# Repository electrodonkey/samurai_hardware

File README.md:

# samurai_hardware
Sumo Robot - Main Board

## Description

This repository contains the hardware design files for the main board of the HIRO 2024 sumo robot. The main board is responsible for the following tasks:

- Running the control algorithm
- Optical sensor reading
- Reading IMU data
- Communicating with the motor drivers

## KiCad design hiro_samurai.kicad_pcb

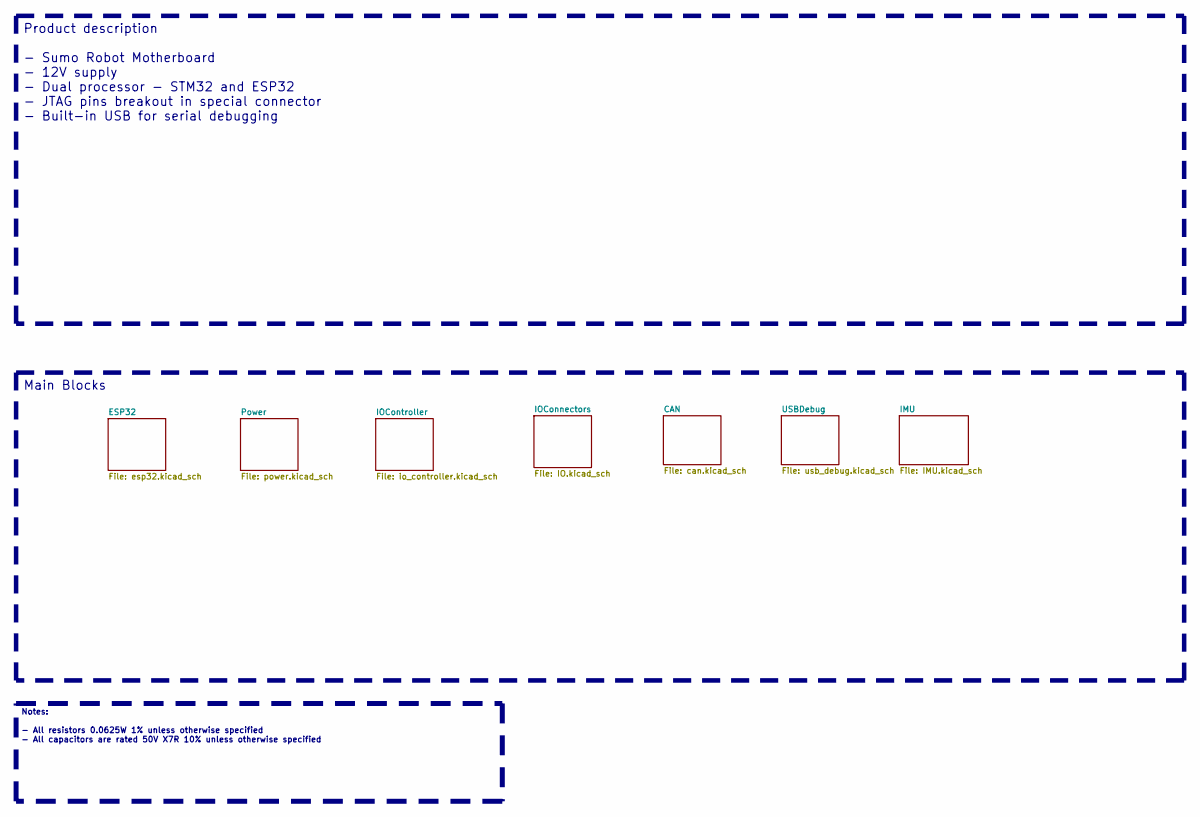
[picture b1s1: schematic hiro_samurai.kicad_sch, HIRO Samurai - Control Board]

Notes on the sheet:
Product description - Sumo Robot Motherboard - 12V supply - Dual processor - STM32 and ESP32 - JTAG pins breakout in special connector - Built-in USB for serial debugging
Notes: - All resistors 0.0625W 1% unless otherwise specified - All capacitors are rated 50V X7R 10% unless otherwise specified
Main Blocks

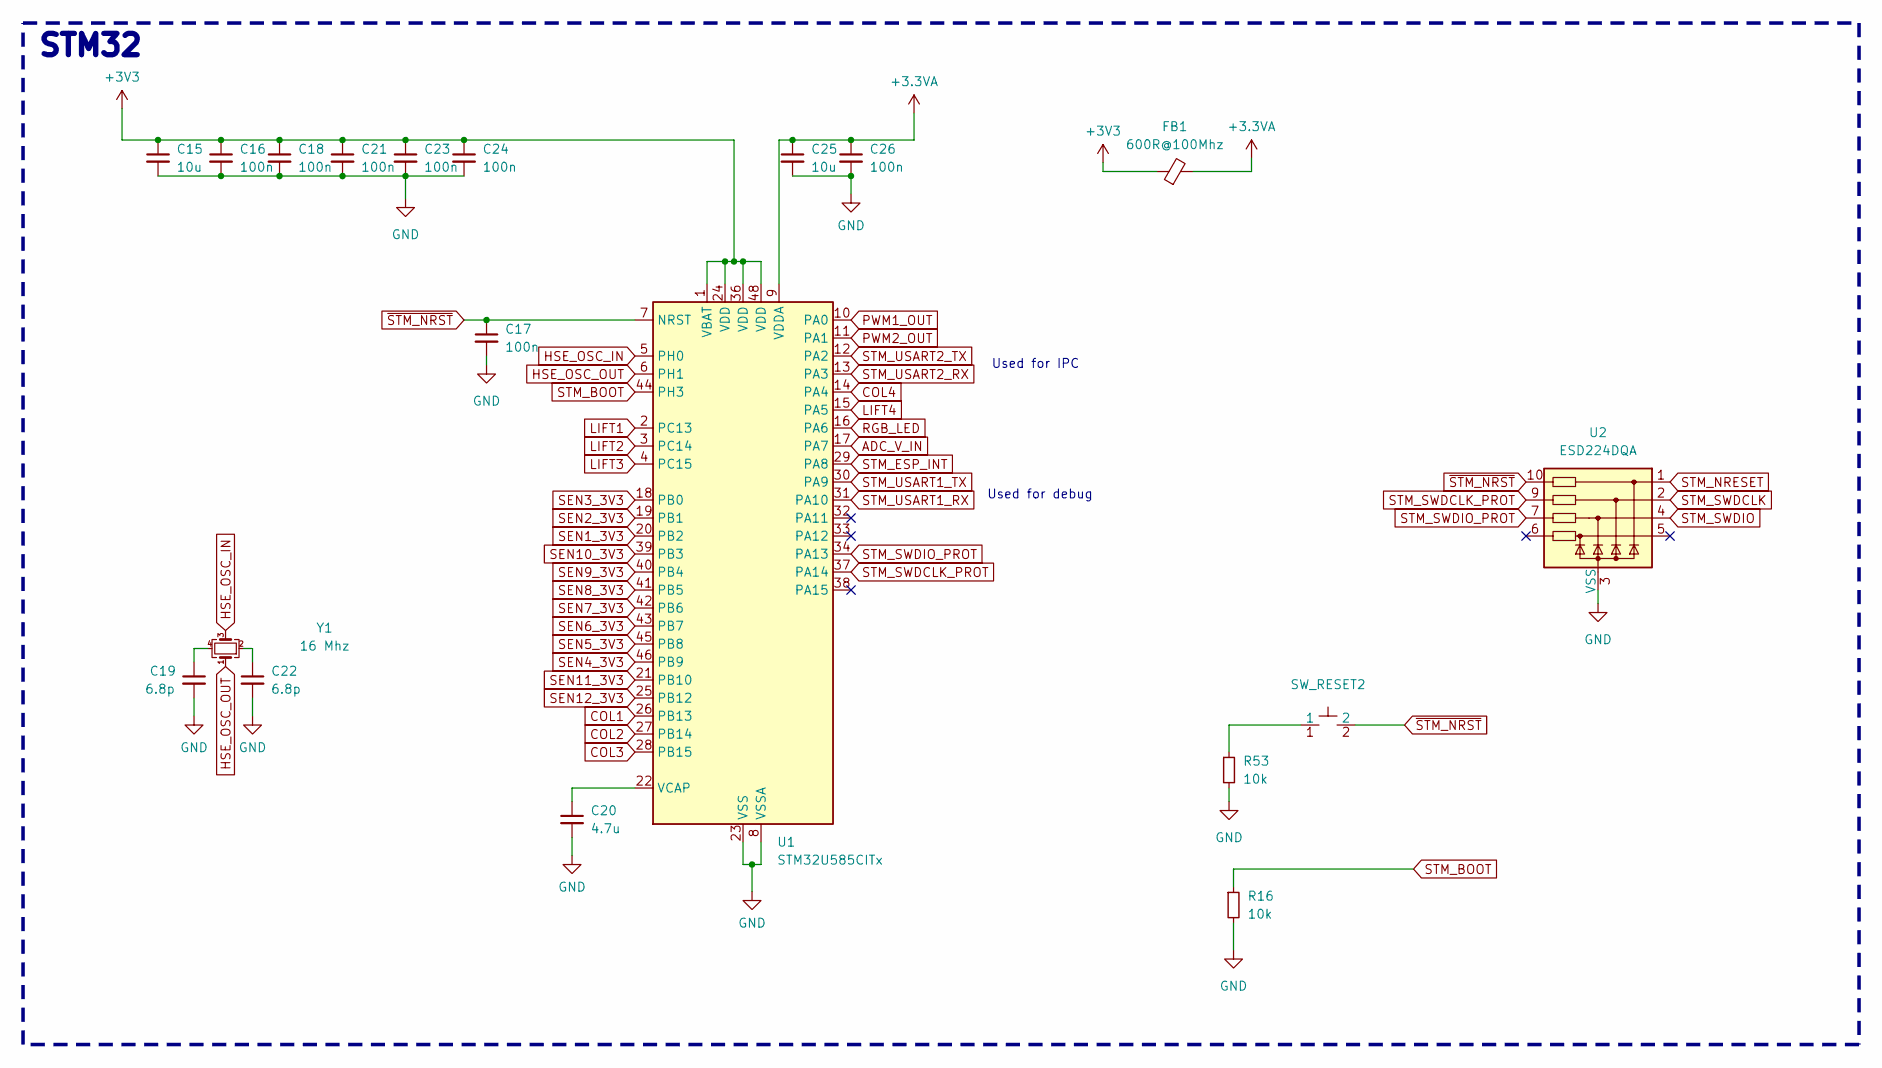
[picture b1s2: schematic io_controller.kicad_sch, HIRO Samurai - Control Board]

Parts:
C15, C25: 10u; C_0603_1608Metric_Pad1.08x0.95mm_HandSolder
C16, C18, C21, C23, C24, C26: 100n; C_0603_1608Metric_Pad1.08x0.95mm_HandSolder
C17: 100n; C_0402_1005Metric_Pad0.74x0.62mm_HandSolder
C19, C22: 6.8p; C_0402_1005Metric_Pad0.74x0.62mm_HandSolder
C20: 4.7u; C_0603_1608Metric_Pad1.08x0.95mm_HandSolder
FB1: 600R@100Mhz; L_0603_1608Metric_Pad1.05x0.95mm_HandSolder
R16, R53: 10k; R_0402_1005Metric_Pad0.72x0.64mm_HandSolder
SW_RESET2: TL1017AABF160QG
U1: STM32U585CITx; LQFP-48_7x7mm_P0.5mm
U2: ESD224DQA; Diodes_UDFN-10_1.0x2.5mm_P0.5mm
Y1: 16 Mhz; Crystal_SMD_2016-4Pin_2.0x1.6mm

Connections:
+3.3VA: C25.1, C26.1, FB1.2, U1.9 (VDDA)
+3V3: C15.1, C16.1, C18.1, C21.1, C23.1, C24.1, FB1.1, U1.1 (VBAT), U1.24 (VDD), U1.36 (VDD), U1.48 (VDD); also elsewhere on the board
ADC_V_IN: U1.17 (PA7); also elsewhere on the board
COL1: U1.26 (PB13); also elsewhere on the board
COL2: U1.27 (PB14); also elsewhere on the board
COL3: U1.28 (PB15); also elsewhere on the board
COL4: U1.14 (PA4); also elsewhere on the board
GND: C15.2, C16.2, C17.2, C18.2, C19.2, C20.2, C21.2, C22.2, C23.2, C24.2, C25.2, C26.2, R16.2, R53.2, U1.8 (VSSA), U1.23 (VSS), U1.35 (VSS), U1.47 (VSS), U2.3 (VSS), U2.8 (VSS); also elsewhere on the board
HSE_OSC_IN: U1.5 (PH0), Y1.3
HSE_OSC_OUT: U1.6 (PH1), Y1.1
LIFT1: U1.2 (PC13); also elsewhere on the board
LIFT2: U1.3 (PC14); also elsewhere on the board
LIFT3: U1.4 (PC15); also elsewhere on the board
LIFT4: U1.15 (PA5); also elsewhere on the board
unnamed: C19.1, Y1.4
unnamed: C22.1, Y1.2
unnamed: R53.1, SW_RESET2.1
unnamed: C20.1, U1.22 (VCAP)
PWM1_OUT: U1.10 (PA0); also elsewhere on the board
PWM2_OUT: U1.11 (PA1); also elsewhere on the board
RGB_LED: U1.16 (PA6); also elsewhere on the board
SEN1_3V3: U1.20 (PB2); also elsewhere on the board
SEN2_3V3: U1.19 (PB1); also elsewhere on the board
SEN3_3V3: U1.18 (PB0); also elsewhere on the board
SEN4_3V3: U1.46 (PB9); also elsewhere on the board
SEN5_3V3: U1.45 (PB8); also elsewhere on the board
SEN6_3V3: U1.43 (PB7); also elsewhere on the board
SEN7_3V3: U1.42 (PB6); also elsewhere on the board
SEN8_3V3: U1.41 (PB5); also elsewhere on the board
SEN9_3V3: U1.40 (PB4); also elsewhere on the board
SEN10_3V3: U1.39 (PB3); also elsewhere on the board
SEN11_3V3: U1.21 (PB10); also elsewhere on the board
SEN12_3V3: U1.25 (PB12); also elsewhere on the board
STM_BOOT: R16.1, U1.44 (PH3)
STM_ESP_INT: U1.29 (PA8); also elsewhere on the board
STM_NRESET: U2.1; also elsewhere on the board
STM_SWDCLK: U2.2; also elsewhere on the board
STM_SWDCLK_PROT: U1.37 (PA14), U2.9
STM_SWDIO: U2.4; also elsewhere on the board
STM_SWDIO_PROT: U1.34 (PA13), U2.7
STM_USART1_RX: U1.31 (PA10); also elsewhere on the board
STM_USART1_TX: U1.30 (PA9); also elsewhere on the board
STM_USART2_RX: U1.13 (PA3); also elsewhere on the board
STM_USART2_TX: U1.12 (PA2); also elsewhere on the board
~STM_NRST: C17.1, SW_RESET2.2, U1.7 (NRST), U2.10

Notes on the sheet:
Used for IPC
Used for debug
STM32

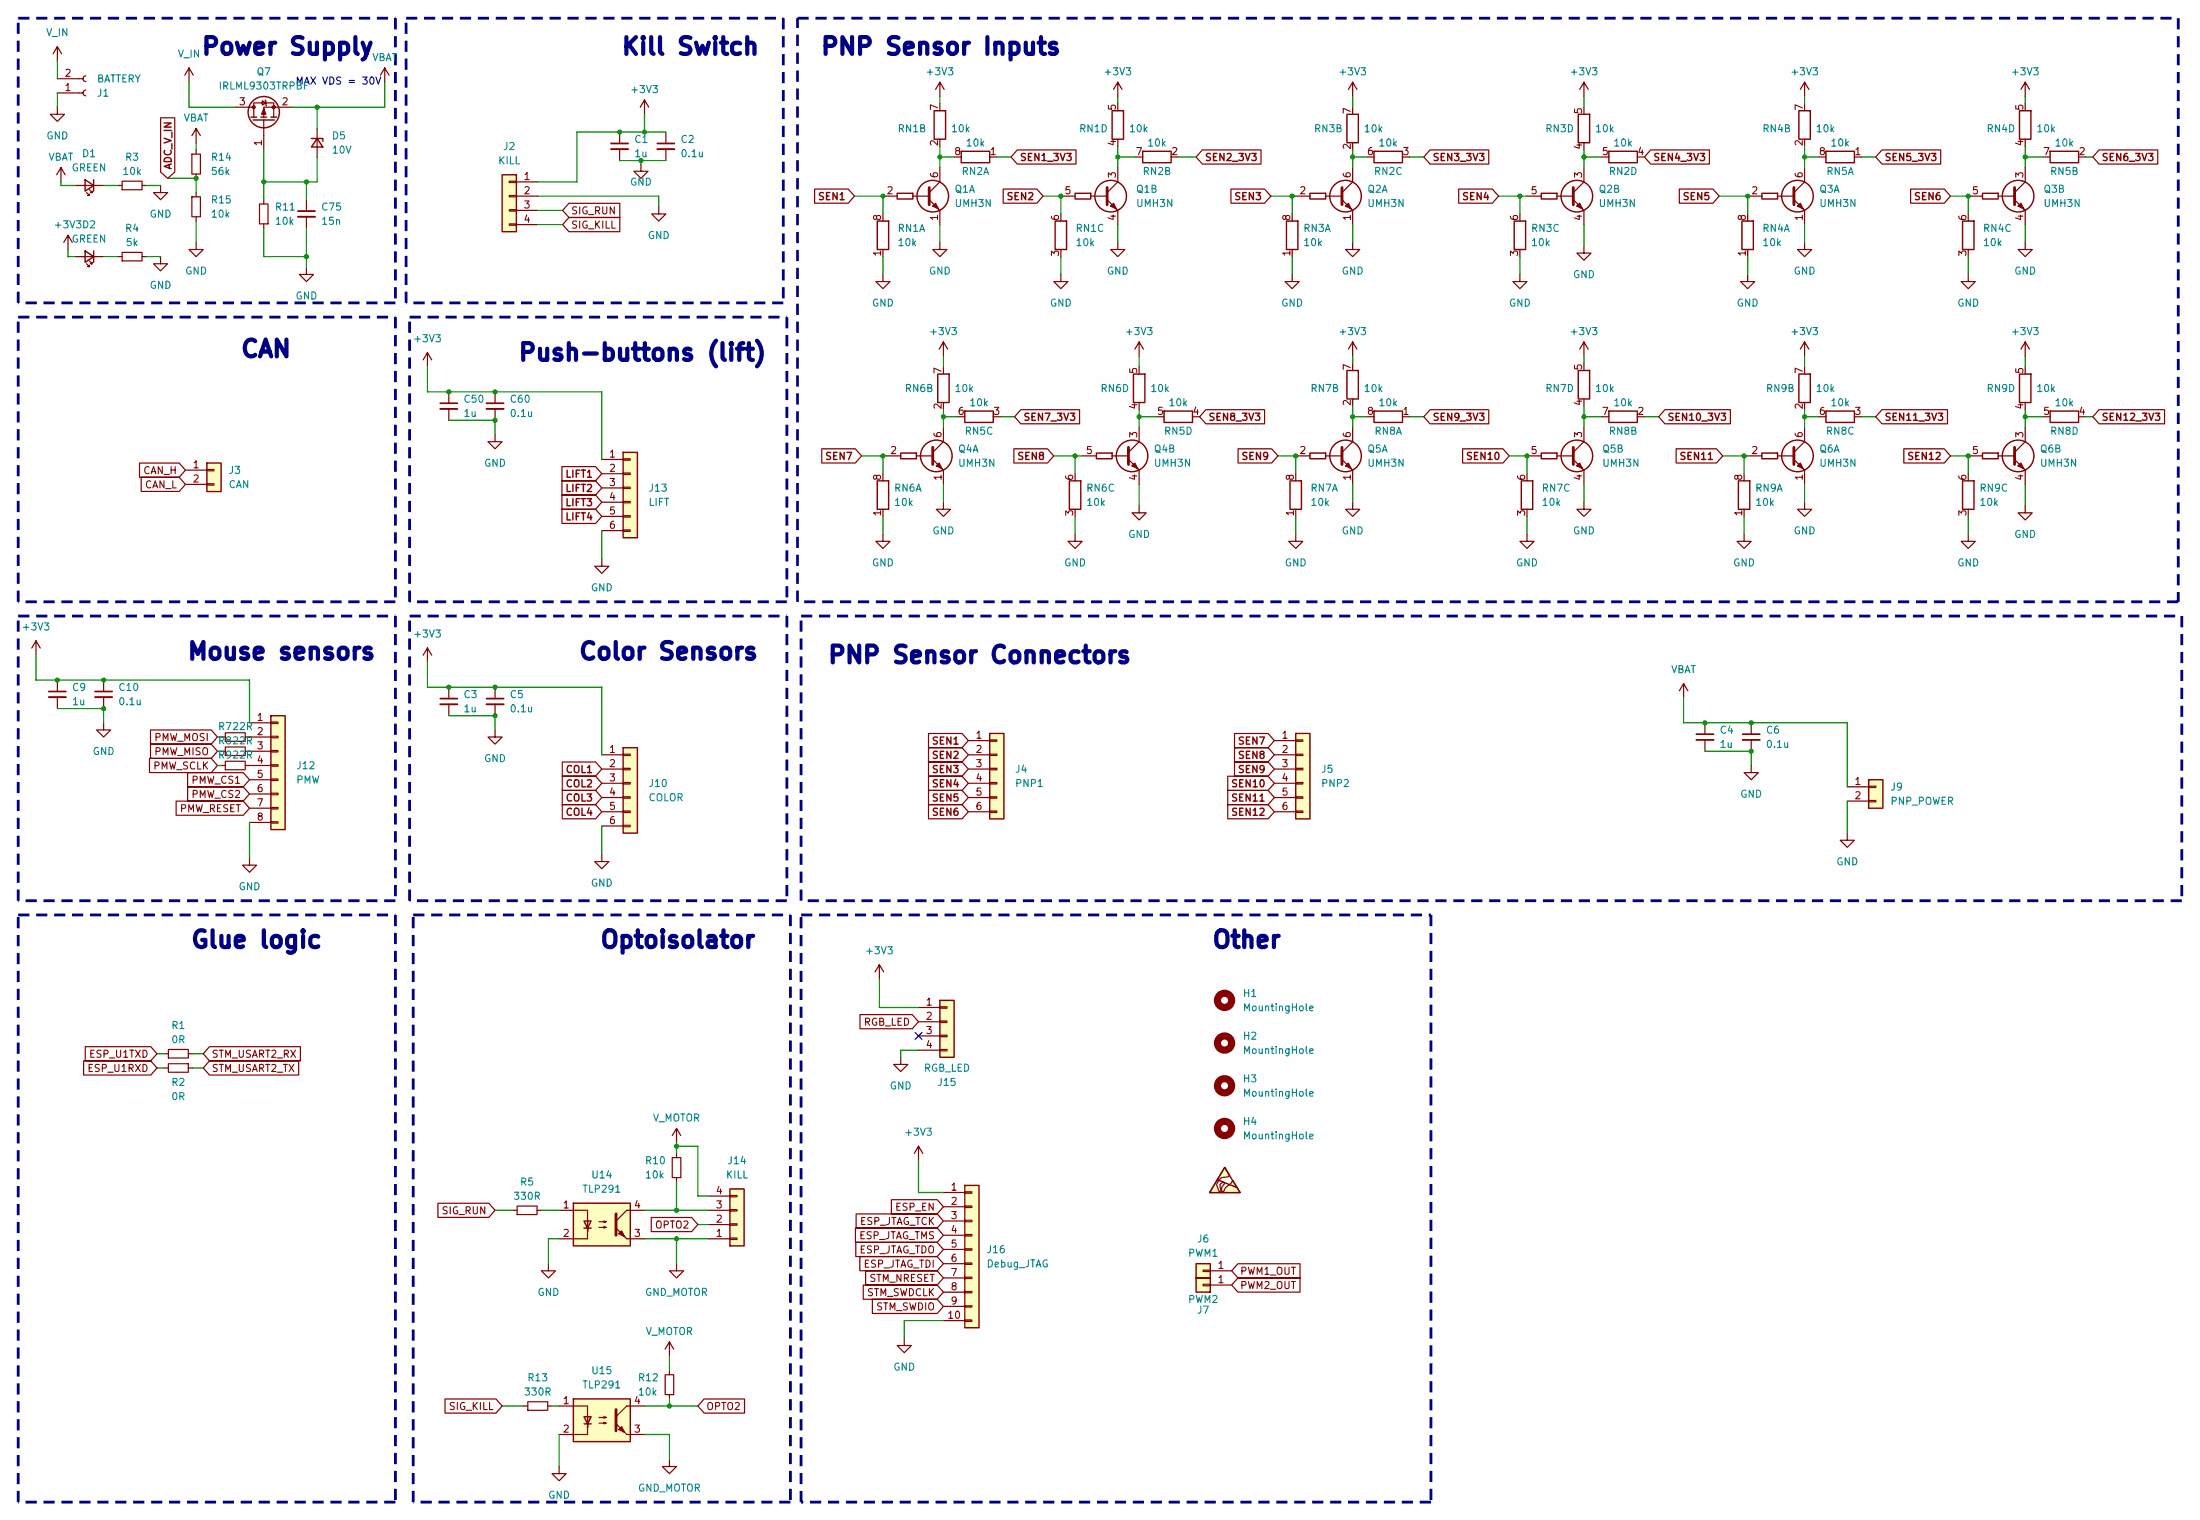
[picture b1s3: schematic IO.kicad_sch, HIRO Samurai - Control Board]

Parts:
C1, C3, C9, C50: 1u; C_0603_1608Metric
C2, C5, C10, C60: 0.1u; C_0603_1608Metric
C4: 1u; C_1210_3225Metric_Pad1.33x2.70mm_HandSolder
C6: 0.1u; C_0805_2012Metric_Pad1.18x1.45mm_HandSolder
C75: 15n; C_0603_1608Metric_Pad1.08x0.95mm_HandSolder
D1, D2: GREEN; LED_0603_1608Metric_Pad1.05x0.95mm_HandSolder
D5: 10V; D_SOD-123
H1, H2, H3, H4: MountingHole; MountingHole_3.2mm_M3
J1: BATTERY; AMASS_XT30U-M_1x02_P5.0mm_Vertical
J2, J14: KILL; Molex_Nano-Fit_105309-xx04_1x04_P2.50mm_Vertical
J3: CAN; Molex_Nano-Fit_105309-xx02_1x02_P2.50mm_Vertical
J4: PNP1; Molex_Nano-Fit_105309-xx06_1x06_P2.50mm_Vertical
J5: PNP2; Molex_Nano-Fit_105309-xx06_1x06_P2.50mm_Vertical
J6: PWM1; SolderWirePad_1x01_SMD_1x2mm
J7: PWM2; SolderWirePad_1x01_SMD_1x2mm
J9: PNP_POWER; Molex_Nano-Fit_105309-xx02_1x02_P2.50mm_Vertical
J10: COLOR; Molex_Nano-Fit_105309-xx06_1x06_P2.50mm_Vertical
J12: PMW; Molex_Nano-Fit_105309-xx08_1x08_P2.50mm_Vertical
J13: LIFT; Molex_Nano-Fit_105309-xx06_1x06_P2.50mm_Vertical
J15: RGB_LED; PinHeader_1x04_P1.27mm_Vertical_SMD_Pin1Left
J16: Debug_JTAG; PinHeader_2x05_P1.27mm_Vertical_SMD
Q1, Q2, Q3, Q4, Q5, Q6: UMH3N; SOT-363_SC-70-6
Q7: IRLML9303TRPBF; SOT-23
R1, R2: 0R; R_0402_1005Metric_Pad0.72x0.64mm_HandSolder
R3, R11, R15: 10k; R_0603_1608Metric_Pad0.98x0.95mm_HandSolder
R4: 5k; R_0603_1608Metric_Pad0.98x0.95mm_HandSolder
R5, R13: 330R; R_0402_1005Metric_Pad0.72x0.64mm_HandSolder
R7, R8, R9: 22R; R_0402_1005Metric_Pad0.72x0.64mm_HandSolder
R10, R12: 10k; R_0402_1005Metric_Pad0.72x0.64mm_HandSolder
R14: 56k; R_0603_1608Metric_Pad0.98x0.95mm_HandSolder
RN1, RN2, RN3, RN4, RN5, RN6, RN7, RN8, RN9: 10k; R_Array_Concave_4x0603
U14, U15: TLP291; SOIC-4_4.55x2.6mm_P1.27mm

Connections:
+3V3: C1.1, C2.1, C3.1, C5.1, C9.1, C10.1, C50.1, C60.1, D2.2 (A), J2.1, J10.1, J12.1, J13.1, J15.1, J16.1, RN1.5 (R4.2), RN1.7 (R2.2), RN3.5 (R4.2), RN3.7 (R2.2), RN4.5 (R4.2), RN4.7 (R2.2), RN6.5 (R4.2), RN6.7 (R2.2), RN7.5 (R4.2), RN7.7 (R2.2), RN9.5 (R4.2), RN9.7 (R2.2); also elsewhere on the board
ADC_V_IN: R14.2, R15.1; also elsewhere on the board
CAN_H: J3.1; also elsewhere on the board
CAN_L: J3.2; also elsewhere on the board
COL1: J10.2; also elsewhere on the board
COL2: J10.3; also elsewhere on the board
COL3: J10.4; also elsewhere on the board
COL4: J10.5; also elsewhere on the board
ESP_EN: J16.2; also elsewhere on the board
ESP_JTAG_TCK: J16.3; also elsewhere on the board
ESP_JTAG_TDI: J16.6; also elsewhere on the board
ESP_JTAG_TDO: J16.5; also elsewhere on the board
ESP_JTAG_TMS: J16.4; also elsewhere on the board
ESP_U1RXD: R2.2; also elsewhere on the board
ESP_U1TXD: R1.1; also elsewhere on the board
GND: C1.2, C2.2, C3.2, C4.2, C5.2, C6.2, C9.2, C10.2, C50.2, C60.2, C75.2, J1.1, J2.2, J9.2, J10.6, J12.8, J13.6, J15.4, J16.10, Q1.1 (E1), Q1.4 (E2), Q2.1 (E1), Q2.4 (E2), Q3.1 (E1), Q3.4 (E2), Q4.1 (E1), Q4.4 (E2), Q5.1 (E1), Q5.4 (E2), Q6.1 (E1), Q6.4 (E2), R3.2, R4.2, R11.1, R15.2, RN1.1 (R1.1), RN1.3 (R3.1), RN3.1 (R1.1), RN3.3 (R3.1), RN4.1 (R1.1), RN4.3 (R3.1), RN6.1 (R1.1), RN6.3 (R3.1), RN7.1 (R1.1), RN7.3 (R3.1), RN9.1 (R1.1), RN9.3 (R3.1), U14.2, U15.2; also elsewhere on the board
GND_MOTOR: J14.1, U14.3, U15.3
LIFT1: J13.2; also elsewhere on the board
LIFT2: J13.3; also elsewhere on the board
LIFT3: J13.4; also elsewhere on the board
LIFT4: J13.5; also elsewhere on the board
unnamed: D1.1 (K), R3.1
unnamed: D2.1 (K), R4.1
unnamed: C75.1, D5.2 (A), Q7.1 (G), R11.2
unnamed: J12.2, R7.2
unnamed: J12.3, R8.2
unnamed: J12.4, R9.2
unnamed: J14.3, R10.1, U14.4
unnamed: Q1.6 (C1), RN1.2 (R2.1), RN2.8 (R1.2)
unnamed: Q1.3 (C2), RN1.4 (R4.1), RN2.7 (R2.2)
unnamed: Q2.6 (C1), RN2.6 (R3.2), RN3.2 (R2.1)
unnamed: Q2.3 (C2), RN2.5 (R4.2), RN3.4 (R4.1)
unnamed: Q3.6 (C1), RN4.2 (R2.1), RN5.8 (R1.2)
unnamed: Q3.3 (C2), RN4.4 (R4.1), RN5.7 (R2.2)
unnamed: Q4.6 (C1), RN5.6 (R3.2), RN6.2 (R2.1)
unnamed: Q4.3 (C2), RN5.5 (R4.2), RN6.4 (R4.1)
unnamed: Q5.6 (C1), RN7.2 (R2.1), RN8.8 (R1.2)
unnamed: Q5.3 (C2), RN7.4 (R4.1), RN8.7 (R2.2)
unnamed: Q6.6 (C1), RN8.6 (R3.2), RN9.2 (R2.1)
unnamed: Q6.3 (C2), RN8.5 (R4.2), RN9.4 (R4.1)
unnamed: R5.2, U14.1
unnamed: R13.2, U15.1
OPTO2: J14.2, R12.1, U15.4
PMW_CS1: J12.5; also elsewhere on the board
PMW_CS2: J12.6; also elsewhere on the board
PMW_MISO: R8.1; also elsewhere on the board
PMW_MOSI: R7.1; also elsewhere on the board
PMW_RESET: J12.7; also elsewhere on the board
PMW_SCLK: R9.1; also elsewhere on the board
PWM1_OUT: J6.1; also elsewhere on the board
PWM2_OUT: J7.1; also elsewhere on the board
RGB_LED: J15.2; also elsewhere on the board
SEN1: J4.1, Q1.2 (B1), RN1.8 (R1.2)
SEN1_3V3: RN2.1 (R1.1); also elsewhere on the board
SEN2: J4.2, Q1.5 (B2), RN1.6 (R3.2)
SEN2_3V3: RN2.2 (R2.1); also elsewhere on the board
SEN3: J4.3, Q2.2 (B1), RN3.8 (R1.2)
SEN3_3V3: RN2.3 (R3.1); also elsewhere on the board
SEN4: J4.4, Q2.5 (B2), RN3.6 (R3.2)
SEN4_3V3: RN2.4 (R4.1); also elsewhere on the board
SEN5: J4.5, Q3.2 (B1), RN4.8 (R1.2)
SEN5_3V3: RN5.1 (R1.1); also elsewhere on the board
SEN6: J4.6, Q3.5 (B2), RN4.6 (R3.2)
SEN6_3V3: RN5.2 (R2.1); also elsewhere on the board
SEN7: J5.1, Q4.2 (B1), RN6.8 (R1.2)
SEN7_3V3: RN5.3 (R3.1); also elsewhere on the board
SEN8: J5.2, Q4.5 (B2), RN6.6 (R3.2)
SEN8_3V3: RN5.4 (R4.1); also elsewhere on the board
SEN9: J5.3, Q5.2 (B1), RN7.8 (R1.2)
SEN9_3V3: RN8.1 (R1.1); also elsewhere on the board
SEN10: J5.4, Q5.5 (B2), RN7.6 (R3.2)
SEN10_3V3: RN8.2 (R2.1); also elsewhere on the board
SEN11: J5.5, Q6.2 (B1), RN9.8 (R1.2)
SEN11_3V3: RN8.3 (R3.1); also elsewhere on the board
SEN12: J5.6, Q6.5 (B2), RN9.6 (R3.2)
SEN12_3V3: RN8.4 (R4.1); also elsewhere on the board
SIG_KILL: J2.4, R13.1; also elsewhere on the board
SIG_RUN: J2.3, R5.1; also elsewhere on the board
STM_NRESET: J16.7; also elsewhere on the board
STM_SWDCLK: J16.8; also elsewhere on the board
STM_SWDIO: J16.9; also elsewhere on the board
STM_USART2_RX: R1.2; also elsewhere on the board
STM_USART2_TX: R2.1; also elsewhere on the board
VBAT: C4.1, C6.1, D1.2 (A), D5.1 (K), J9.1, Q7.2 (S), R14.1; also elsewhere on the board
V_IN: J1.2, Q7.3 (D)
V_MOTOR: J14.4, R10.2, R12.2

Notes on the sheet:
Optoisolator
Kill Switch
Power Supply
Glue logic
PNP Sensor Inputs
Color Sensors
Other
CAN
PNP Sensor Connectors
Push-buttons (lift)
MAX VDS = 30V
Mouse sensors

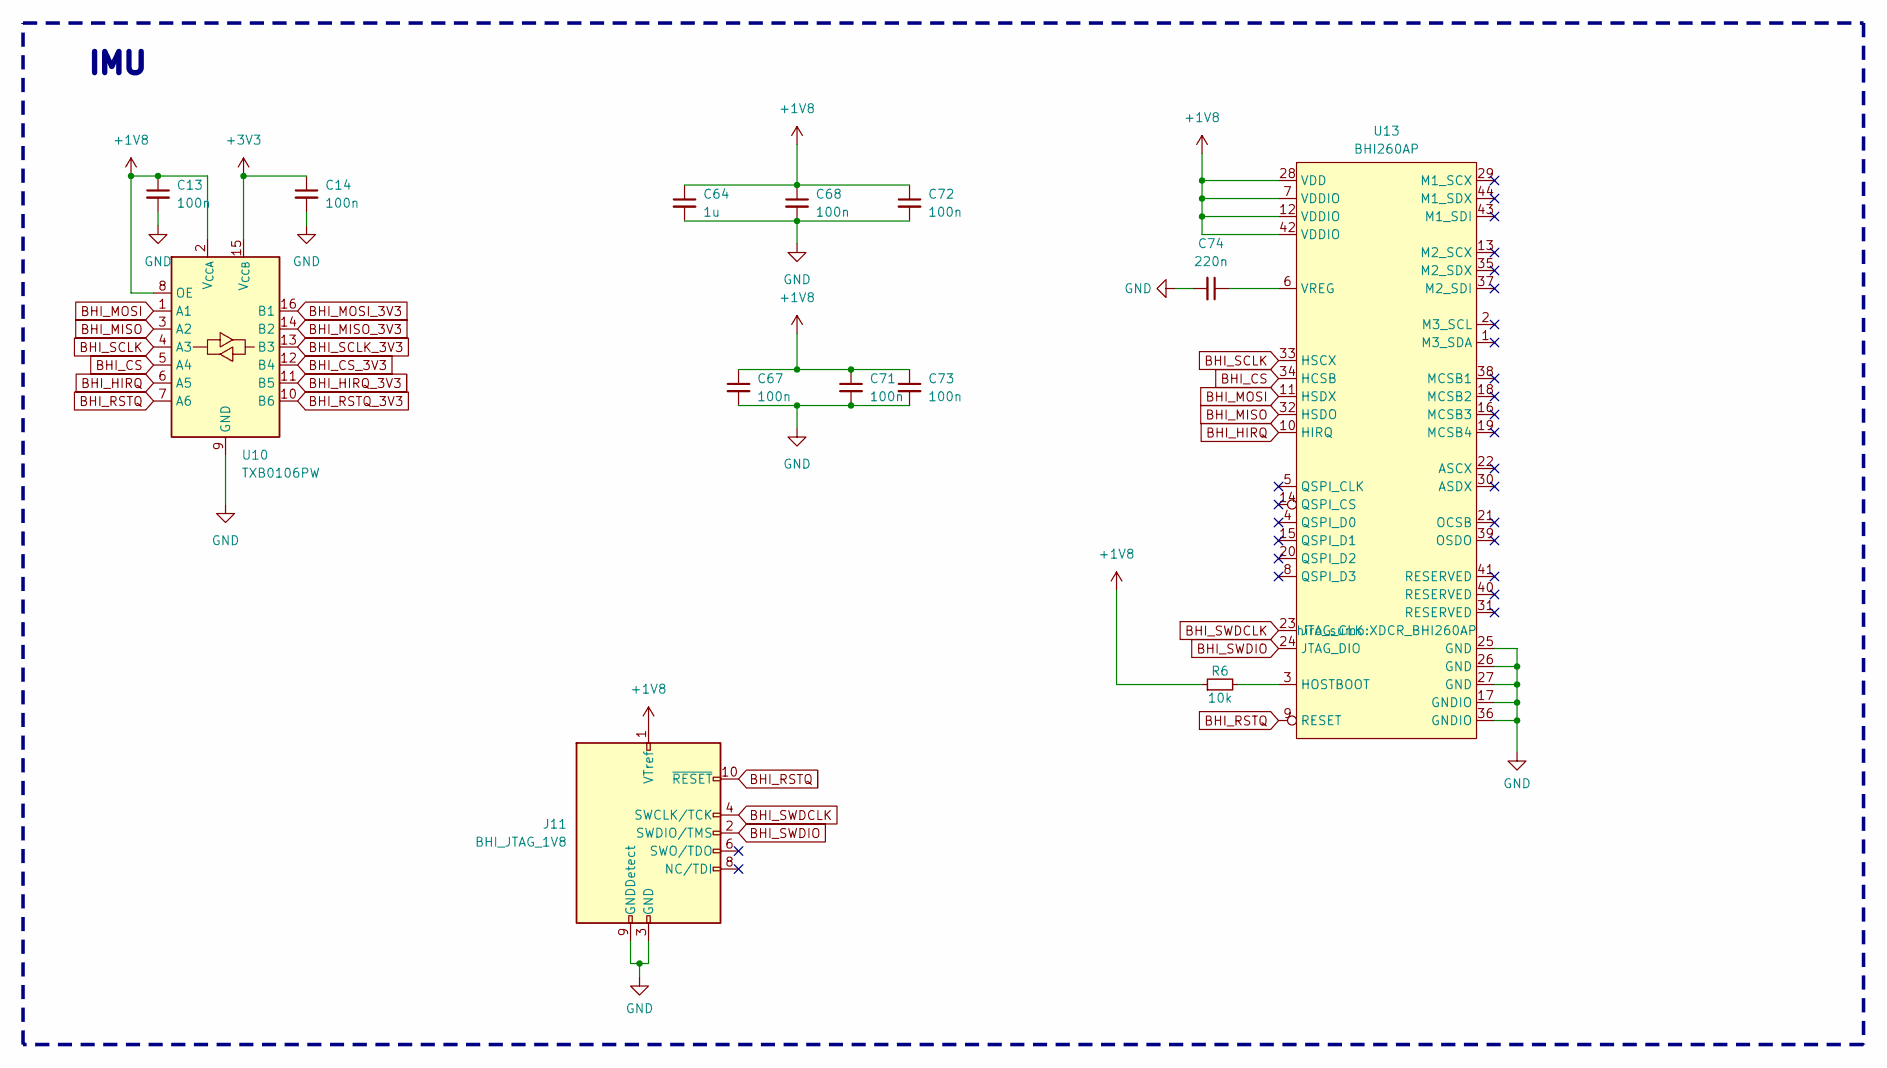
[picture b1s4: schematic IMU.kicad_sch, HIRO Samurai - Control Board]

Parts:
C13, C14, C67, C68, C71, C72, C73: 100n; C_0402_1005Metric_Pad0.74x0.62mm_HandSolder
C64: 1u; C_0402_1005Metric_Pad0.74x0.62mm_HandSolder
C74: 220n; C_0402_1005Metric_Pad0.74x0.62mm_HandSolder
J11: BHI_JTAG_1V8; PinHeader_2x05_P1.27mm_Vertical_SMD
R6: 10k; R_0402_1005Metric_Pad0.72x0.64mm_HandSolder
U10: TXB0106PW; TSSOP-16_4.4x5mm_P0.65mm
U13: BHI260AP; XDCR_BHI260AP

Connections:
+1V8: C13.1, C64.1, C67.1, C68.1, C71.1, C72.1, C73.1, J11.1 (VTref), R6.1, U10.2 (V_{CCA}), U10.8 (OE), U13.7 (VDDIO), U13.12 (VDDIO), U13.28 (VDD), U13.42 (VDDIO); also elsewhere on the board
+3V3: C14.1, U10.15 (V_{CCB}); also elsewhere on the board
BHI_CS: U10.5 (A4), U13.34 (HCSB)
BHI_CS_3V3: U10.12 (B4); also elsewhere on the board
BHI_HIRQ: U10.6 (A5), U13.10 (HIRQ)
BHI_HIRQ_3V3: U10.11 (B5); also elsewhere on the board
BHI_MISO: U10.3 (A2), U13.32 (HSDO)
BHI_MISO_3V3: U10.14 (B2); also elsewhere on the board
BHI_MOSI: U10.1 (A1), U13.11 (HSDX)
BHI_MOSI_3V3: U10.16 (B1); also elsewhere on the board
BHI_RSTQ: J11.10 (~RESET), U10.7 (A6), U13.9 (RESET)
BHI_RSTQ_3V3: U10.10 (B6); also elsewhere on the board
BHI_SCLK: U10.4 (A3), U13.33 (HSCX)
BHI_SCLK_3V3: U10.13 (B3); also elsewhere on the board
BHI_SWDCLK: J11.4 (SWCLK/TCK), U13.23 (JTAG_CLK)
BHI_SWDIO: J11.2 (SWDIO/TMS), U13.24 (JTAG_DIO)
GND: C13.2, C14.2, C64.2, C67.2, C68.2, C71.2, C72.2, C73.2, C74.2, J11.3 (GND), J11.5 (GND), J11.9 (GNDDetect), U10.9 (GND), U13.17 (GNDIO), U13.25 (GND), U13.26 (GND), U13.27 (GND), U13.36 (GNDIO); also elsewhere on the board
unnamed: R6.2, U13.3 (HOSTBOOT)
unnamed: C74.1, U13.6 (VREG)

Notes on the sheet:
IMU

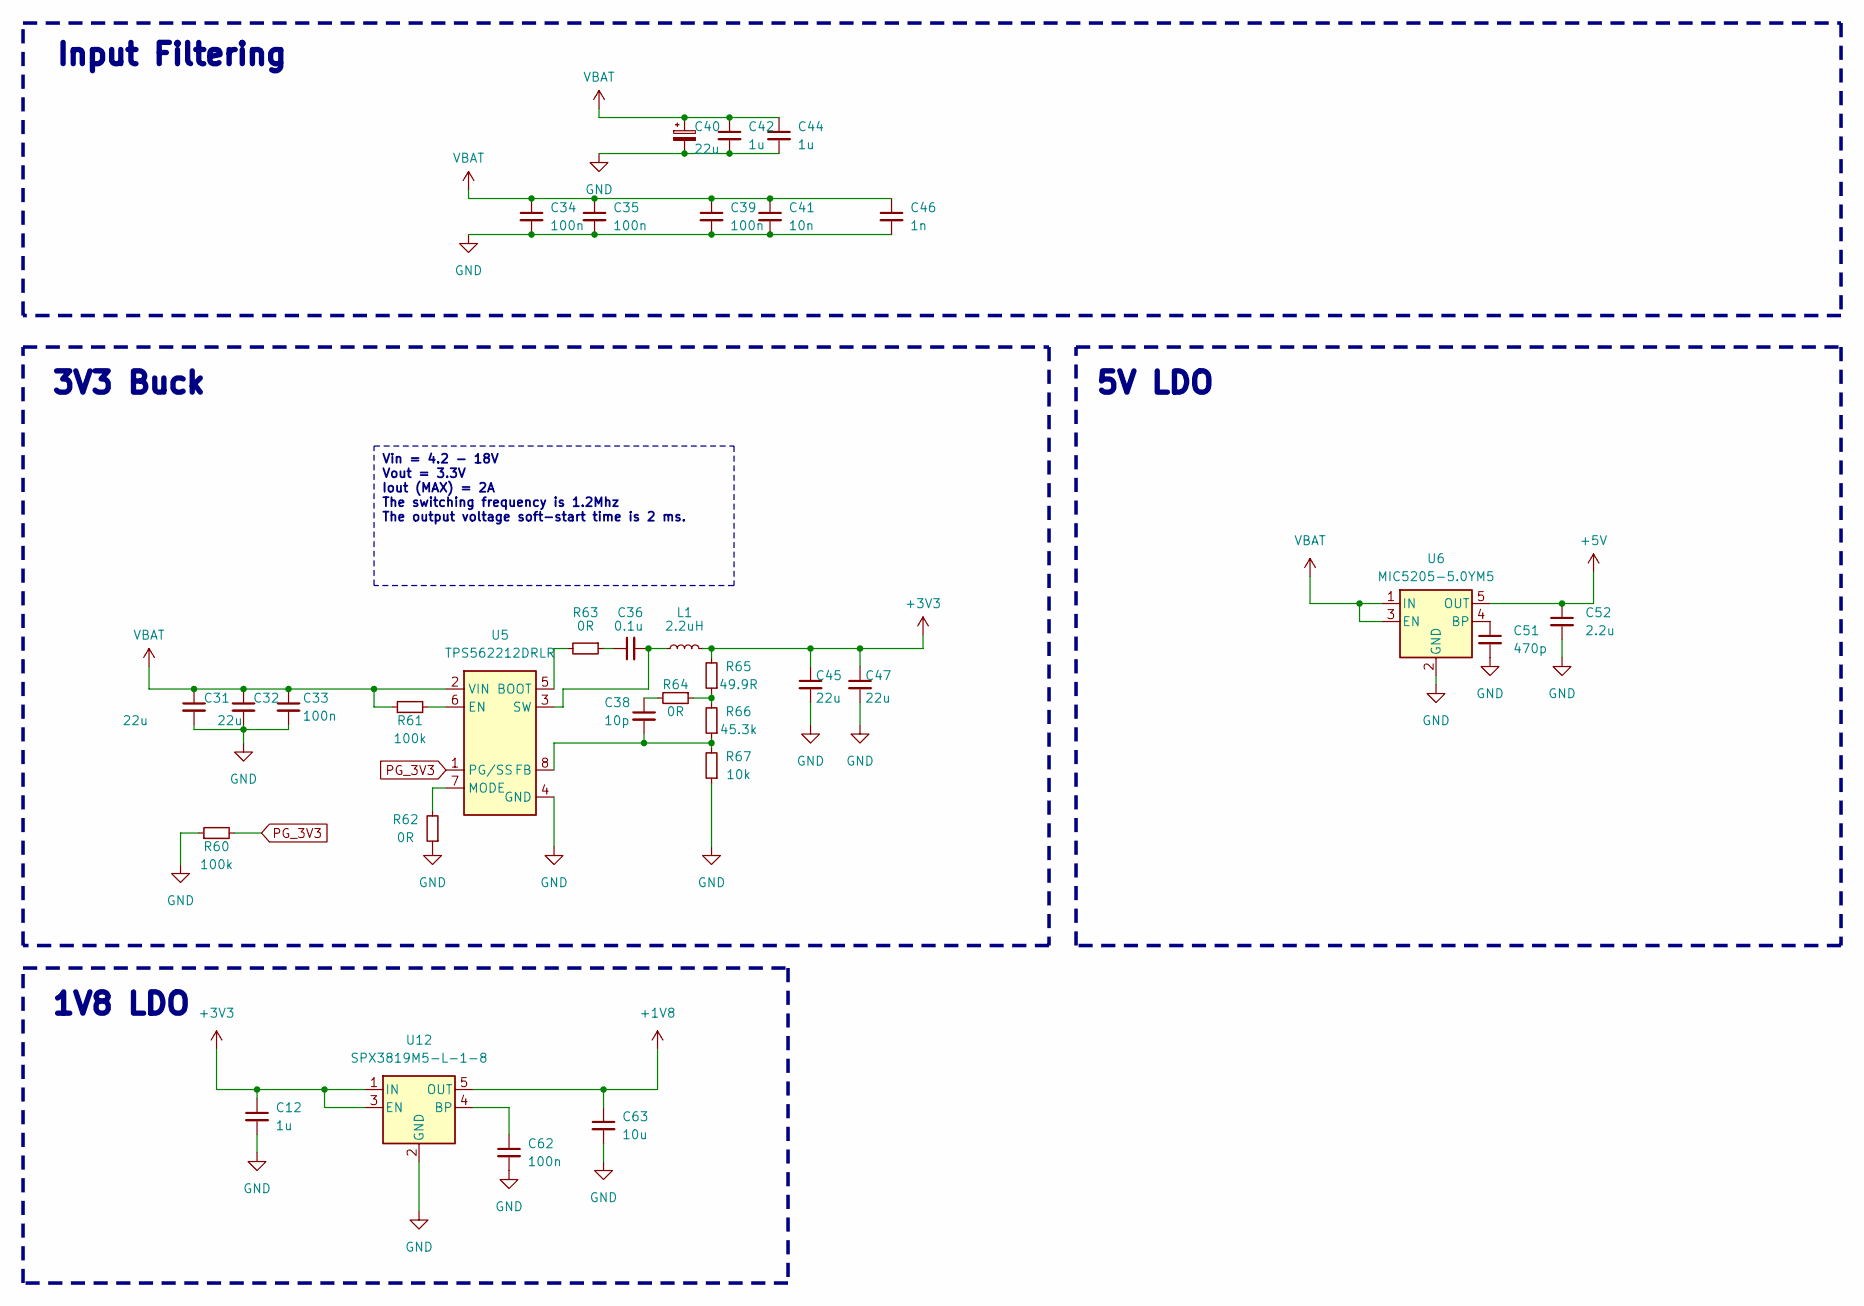
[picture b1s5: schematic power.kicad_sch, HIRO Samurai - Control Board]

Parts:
C12: 1u; C_0402_1005Metric_Pad0.74x0.62mm_HandSolder
C31, C32, C45, C47: 22u; C_0603_1608Metric_Pad1.08x0.95mm_HandSolder
C33, C62: 100n; C_0402_1005Metric_Pad0.74x0.62mm_HandSolder
C34, C35, C39: 100n; C_0603_1608Metric_Pad1.08x0.95mm_HandSolder
C36: 0.1u; C_0402_1005Metric_Pad0.74x0.62mm_HandSolder
C38: 10p; C_0402_1005Metric_Pad0.74x0.62mm_HandSolder
C40: 22u; CP_Elec_4x4.5
C41: 10n; C_0603_1608Metric_Pad1.08x0.95mm_HandSolder
C42, C44: 1u; C_1210_3225Metric_Pad1.33x2.70mm_HandSolder
C46: 1n; C_0603_1608Metric_Pad1.08x0.95mm_HandSolder
C51: 470p; C_0402_1005Metric_Pad0.74x0.62mm_HandSolder
C52: 2.2u; C_0603_1608Metric_Pad1.08x0.95mm_HandSolder
C63: 10u; C_0603_1608Metric_Pad1.08x0.95mm_HandSolder
L1: 2.2uH; L_Bourns_SRP1038C_10.0x10.0mm
R60, R61: 100k; R_0402_1005Metric_Pad0.72x0.64mm_HandSolder
R62, R63, R64: 0R; R_0402_1005Metric_Pad0.72x0.64mm_HandSolder
R65: 49.9R; R_0402_1005Metric
R66: 45.3k; R_0402_1005Metric
R67: 10k; R_0402_1005Metric
U5: TPS562212DRLR; SOT-583-8
U6: MIC5205-5.0YM5; SOT-23-5
U12: SPX3819M5-L-1-8; SOT-23-5

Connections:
+1V8: C63.1, U12.5 (OUT); also elsewhere on the board
+3V3: C12.1, C45.1, C47.1, L1.2, R65.2, U12.1 (IN), U12.3 (EN); also elsewhere on the board
+5V: C52.1, U6.5 (OUT); also elsewhere on the board
GND: C12.2, C31.2, C32.2, C33.2, C34.2, C35.2, C39.2, C40.2, C41.2, C42.2, C44.2, C45.2, C46.2, C47.2, C51.2, C52.2, C62.2, C63.2, R60.1, R62.1, R67.1, U5.4 (GND), U6.2 (GND), U12.2 (GND); also elsewhere on the board
unnamed: C36.1, R63.1
unnamed: C38.1, R64.2
unnamed: R64.1, R65.1, R66.2
unnamed: R63.2, U5.5 (BOOT)
unnamed: R61.2, U5.6 (EN)
unnamed: C38.2, R66.1, R67.2, U5.8 (FB)
unnamed: R62.2, U5.7 (MODE)
unnamed: C36.2, L1.1, U5.3 (SW)
unnamed: C51.1, U6.4 (BP)
unnamed: C62.1, U12.4 (BP)
PG_3V3: R60.2, U5.1 (PG/SS)
VBAT: C31.1, C32.1, C33.1, C34.1, C35.1, C39.1, C40.1, C41.1, C42.1, C44.1, C46.1, R61.1, U5.2 (VIN), U6.1 (IN), U6.3 (EN); also elsewhere on the board

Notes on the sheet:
Vin = 4.2 - 18V Vout = 3.3V Iout (MAX) = 2A The switching frequency is 1.2Mhz The output voltage soft-start time is 2 ms.
1V8 LDO
5V LDO
3V3 Buck
Input Filtering

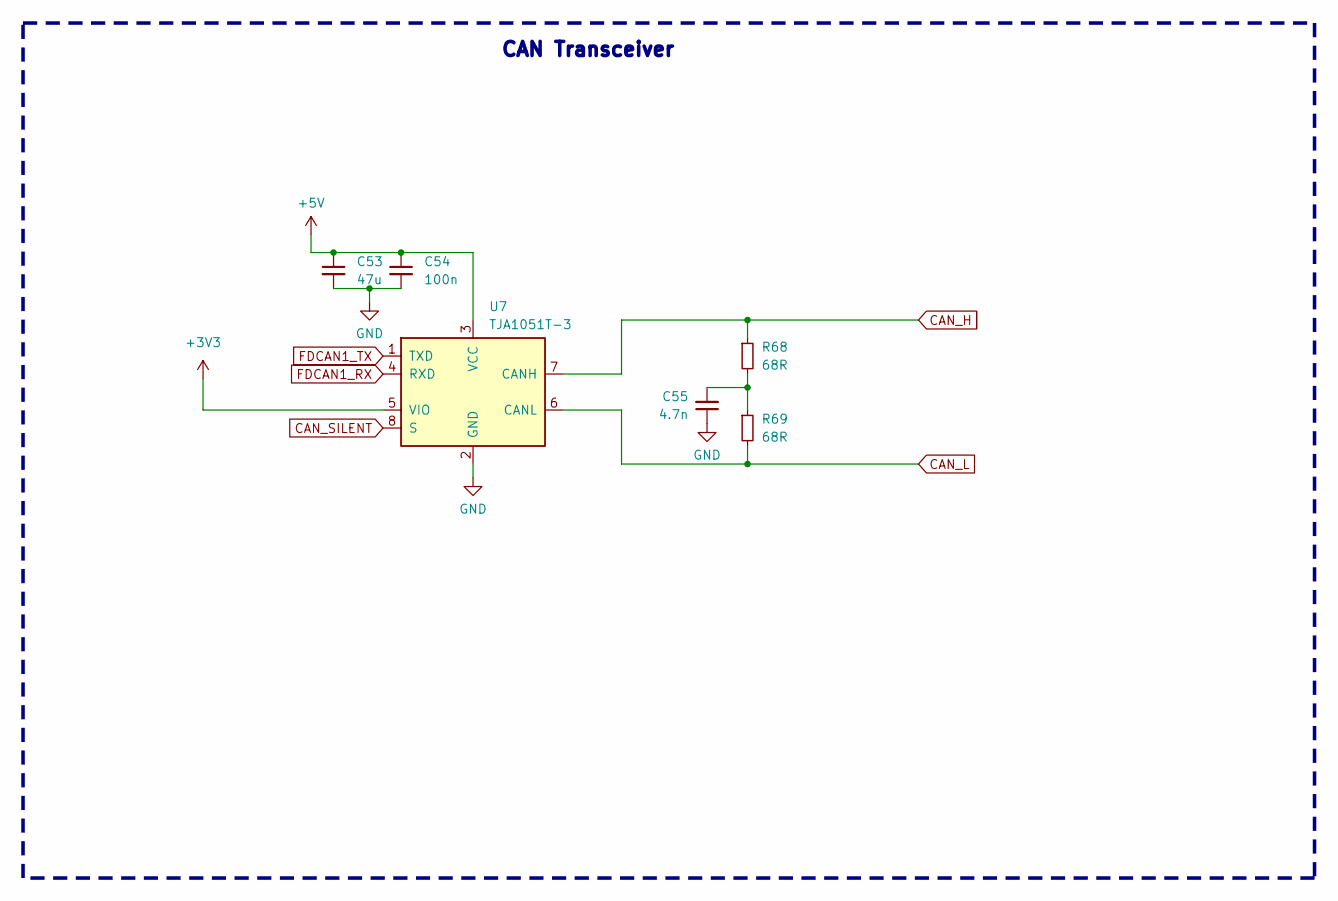
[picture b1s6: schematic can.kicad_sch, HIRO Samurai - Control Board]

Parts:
C53: 47u; C_0603_1608Metric_Pad1.08x0.95mm_HandSolder
C54: 100n; C_0402_1005Metric_Pad0.74x0.62mm_HandSolder
C55: 4.7n; C_0402_1005Metric_Pad0.74x0.62mm_HandSolder
R68, R69: 68R; C_0603_1608Metric_Pad1.08x0.95mm_HandSolder
U7: TJA1051T-3; SOIC-8_3.9x4.9mm_P1.27mm

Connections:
+3V3: U7.5 (VIO); also elsewhere on the board
+5V: C53.1, C54.1, U7.3 (VCC); also elsewhere on the board
CAN_H: R68.1, U7.7 (CANH); also elsewhere on the board
CAN_L: R69.2, U7.6 (CANL); also elsewhere on the board
CAN_SILENT: U7.8 (S); also elsewhere on the board
FDCAN1_RX: U7.4 (RXD); also elsewhere on the board
FDCAN1_TX: U7.1 (TXD); also elsewhere on the board
GND: C53.2, C54.2, C55.1, U7.2 (GND); also elsewhere on the board
unnamed: C55.2, R68.2, R69.1

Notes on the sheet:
CAN Transceiver

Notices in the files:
IMU.kicad_sch:
CC-BY-SA 4.0
